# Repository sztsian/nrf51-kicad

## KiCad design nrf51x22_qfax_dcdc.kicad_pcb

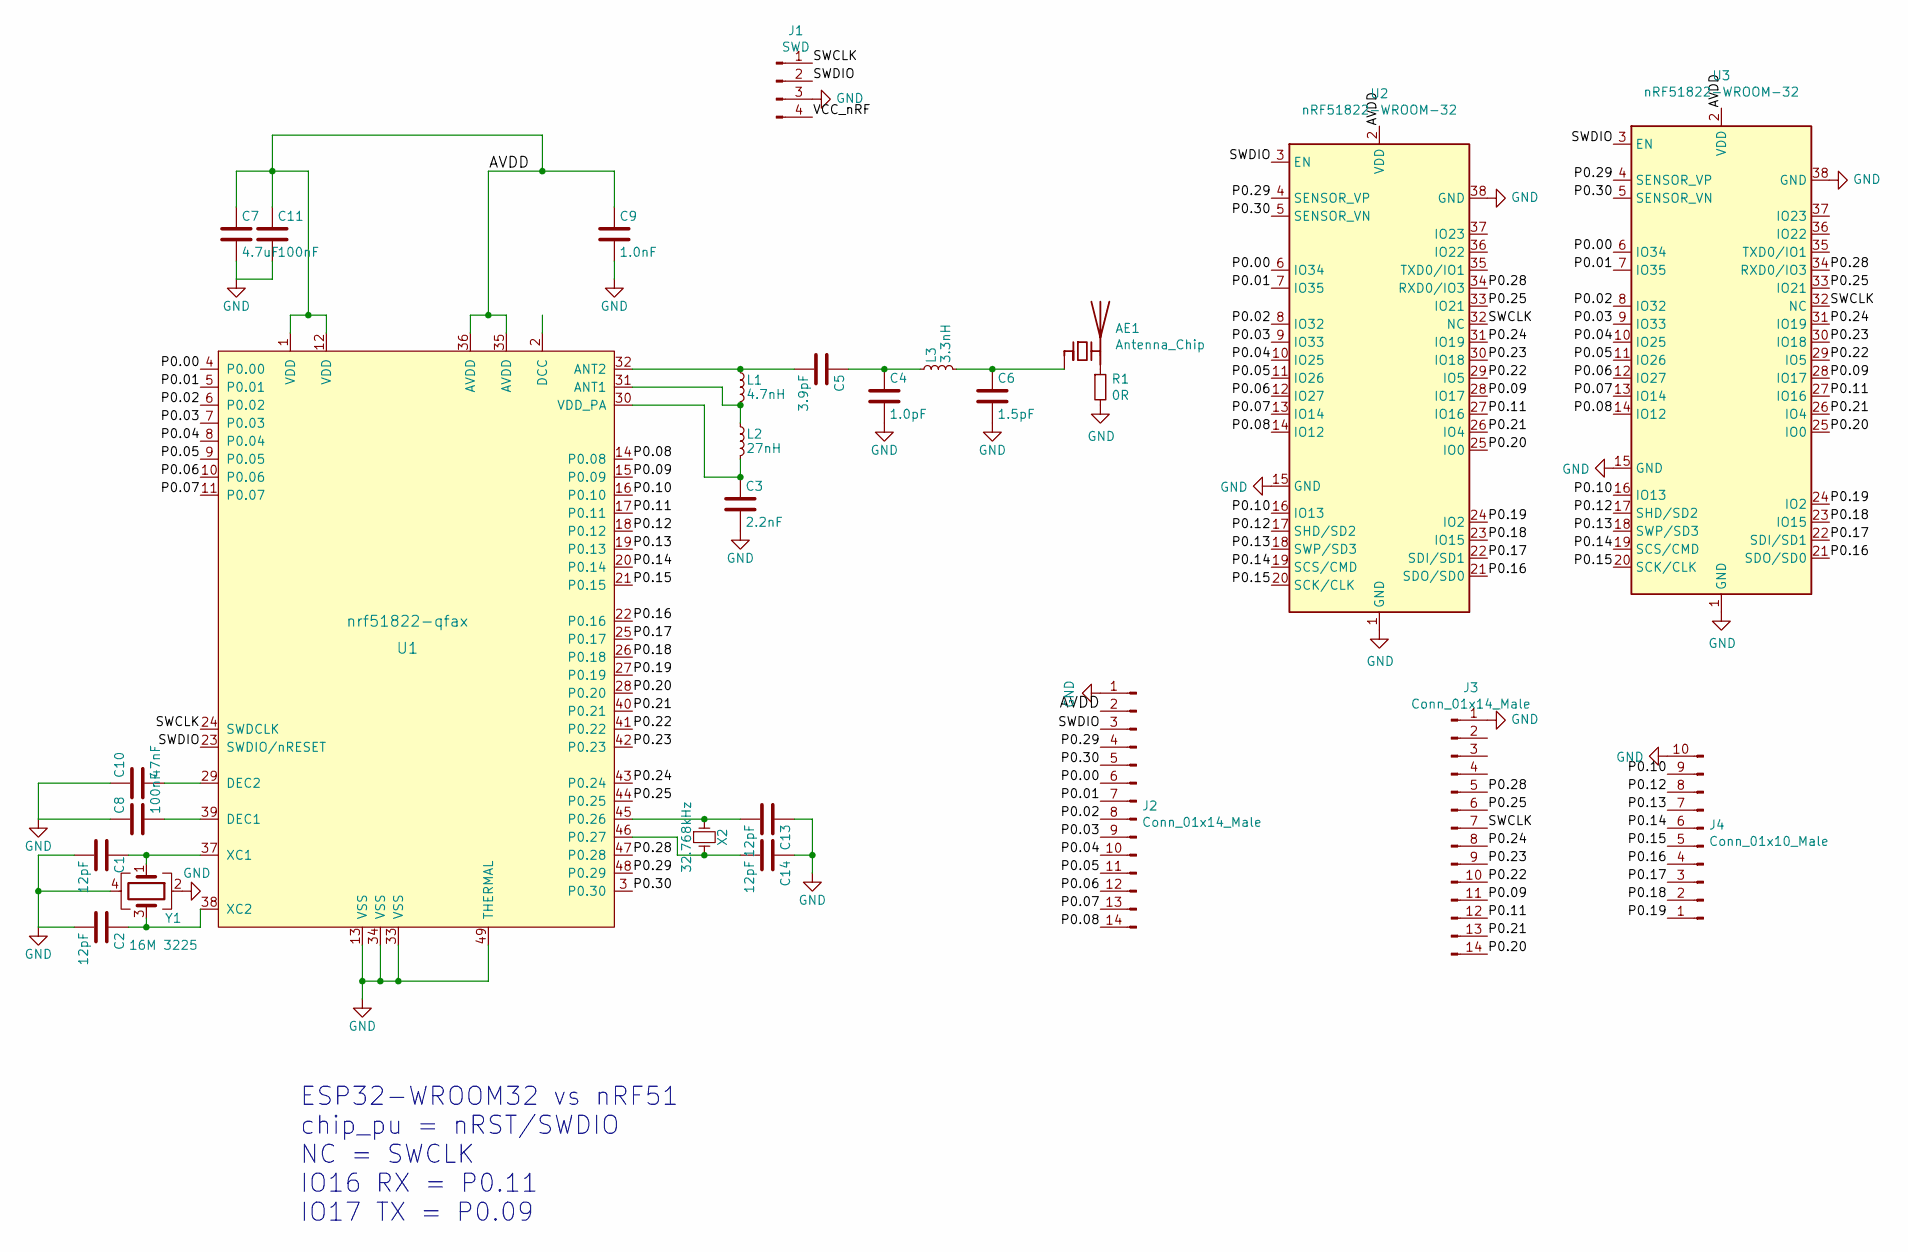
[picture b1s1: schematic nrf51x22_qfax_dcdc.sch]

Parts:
AE1: Antenna_Chip; Texas_SWRA117D_2.4GHz_Left
C1, C2, C13, C14: 12pF; C_0402_1005Metric; Manufacturer Part GRM1555C1H120GA01D
C3: 2.2nF; C_0402_1005Metric; Manufacturer Part CC0402KRX7R9BB222
C4: 1.0pF; C_0402_1005Metric
C5: 3.9pF; C_0402_1005Metric
C6: 1.5pF; C_0402_1005Metric
C7: 4.7uF; C_0402_1005Metric; Manufacturer Part GRM188R61C475KE11D
C8, C11: 100nF; C_0402_1005Metric; Manufacturer Part CC0402KRX7R6BB104
C9: 1.0nF; C_0402_1005Metric; Manufacturer Part CC0402KRX7R9BB102
C10: 47nF; C_0402_1005Metric; Manufacturer Part CC0402KRX7R8BB473
J1: SWD; PinHeader_1x04_P2.54mm_Vertical
J2, J3: Conn_01x14_Male; PinHeader_1x14_P1.27mm_Vertical
J4: Conn_01x10_Male; PinHeader_1x10_P1.27mm_Vertical
L1: 4.7nH; L_0402_1005Metric
L2: 27nH; L_0402_1005Metric
L3: 3.3nH; L_0402_1005Metric
R1: 0R; R_0402_1005Metric
U1: nrf51822-qfax; nrf51-qfax-1ep-vias; Manufacturer Part NRF51822-QFAC-T
U2, U3: nRF51822-WROOM-32; nRF51822-WROOM-32D
X2: 32.768kHz; Crystal_SMD_3215-2Pin_3.2x1.5mm; Manufacturer Part ABS07-32.768KHZ-9-T
Y1: 16M 3225; Crystal_SMD_2520-4Pin_2.5x2.0mm

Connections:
/AVDD: C7.1, C9.1, C11.1, J2.2, U1.1 (VDD), U1.12 (VDD), U1.35 (AVDD), U1.36 (AVDD), U2.2 (VDD), U3.2 (VDD)
/P0.00: J2.6, U1.4 (P0.00), U2.6 (IO34), U3.6 (IO34)
/P0.01: J2.7, U1.5 (P0.01), U2.7 (IO35), U3.7 (IO35)
/P0.02: J2.8, U1.6 (P0.02), U2.8 (IO32), U3.8 (IO32)
/P0.03: J2.9, U1.7 (P0.03), U2.9 (IO33), U3.9 (IO33)
/P0.04: J2.10, U1.8 (P0.04), U2.10 (IO25), U3.10 (IO25)
/P0.05: J2.11, U1.9 (P0.05), U2.11 (IO26), U3.11 (IO26)
/P0.06: J2.12, U1.10 (P0.06), U2.12 (IO27), U3.12 (IO27)
/P0.07: J2.13, U1.11 (P0.07), U2.13 (IO14), U3.13 (IO14)
/P0.08: J2.14, U1.14 (P0.08), U2.14 (IO12), U3.14 (IO12)
/P0.09: J3.11, U1.15 (P0.09), U2.28 (IO17), U3.28 (IO17)
/P0.10: J4.9, U1.16 (P0.10), U2.16 (IO13), U3.16 (IO13)
/P0.11: J3.12, U1.17 (P0.11), U2.27 (IO16), U3.27 (IO16)
/P0.12: J4.8, U1.18 (P0.12), U2.17 (SHD/SD2), U3.17 (SHD/SD2)
/P0.13: J4.7, U1.19 (P0.13), U2.18 (SWP/SD3), U3.18 (SWP/SD3)
/P0.14: J4.6, U1.20 (P0.14), U2.19 (SCS/CMD), U3.19 (SCS/CMD)
/P0.15: J4.5, U1.21 (P0.15), U2.20 (SCK/CLK), U3.20 (SCK/CLK)
/P0.16: J4.4, U1.22 (P0.16), U2.21 (SDO/SD0), U3.21 (SDO/SD0)
/P0.17: J4.3, U1.25 (P0.17), U2.22 (SDI/SD1), U3.22 (SDI/SD1)
/P0.18: J4.2, U1.26 (P0.18), U2.23 (IO15), U3.23 (IO15)
/P0.19: J4.1, U1.27 (P0.19), U2.24 (IO2), U3.24 (IO2)
/P0.20: J3.14, U1.28 (P0.20), U2.25 (IO0), U3.25 (IO0)
/P0.21: J3.13, U1.40 (P0.21), U2.26 (IO4), U3.26 (IO4)
/P0.22: J3.10, U1.41 (P0.22), U2.29 (IO5), U3.29 (IO5)
/P0.23: J3.9, U1.42 (P0.23), U2.30 (IO18), U3.30 (IO18)
/P0.24: J3.8, U1.43 (P0.24), U2.31 (IO19), U3.31 (IO19)
/P0.25: J3.6, U1.44 (P0.25), U2.33 (IO21), U3.33 (IO21)
/P0.28: J3.5, U1.47 (P0.28), U2.34 (RXD0/IO3), U3.34 (RXD0/IO3)
/P0.29: J2.4, U1.48 (P0.29), U2.4 (SENSOR_VP), U3.4 (SENSOR_VP)
/P0.30: J2.5, U1.3 (P0.30), U2.5 (SENSOR_VN), U3.5 (SENSOR_VN)
/SWDIO: J1.2, J2.3, U1.23 (SWDIO/nRESET), U2.3 (EN), U3.3 (EN)
/VCC_nRF: J1.4
GND: C1.2, C2.2, C3.2, C4.2, C6.2, C7.2, C8.1, C9.2, C10.1, C11.2, C13.1, C14.1, J1.3, J2.1, J3.1, J4.10, R1.2, U1.13 (VSS), U1.33 (VSS), U1.34 (VSS), U1.49 (THERMAL), U2.1 (GND), U2.15 (GND), U2.38 (GND), U3.1 (GND), U3.15 (GND), U3.38 (GND), Y1.2, Y1.4
unnamed: AE1.1 (FEED), C6.1, L3.2
unnamed: AE1.2 (PCB_Trace), R1.1
unnamed: C1.1, U1.37 (XC1), Y1.1
unnamed: C2.1, U1.38 (XC2), Y1.3
unnamed: C3.1, L2.2, U1.30 (VDD_PA)
unnamed: C4.1, C5.1, L3.1
unnamed: C5.2, L1.1, U1.32 (ANT2)
unnamed: C8.2, U1.39 (DEC1)
unnamed: C10.2, U1.29 (DEC2)
unnamed: C13.2, U1.45 (P0.26), X2.1
unnamed: C14.2, U1.46 (P0.27), X2.2
unnamed: L1.2, L2.1, U1.31 (ANT1)

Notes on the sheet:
ESP32-WROOM32 vs nRF51 chip_pu = nRST/SWDIO NC = SWCLK IO16 RX = P0.11 IO17 TX = P0.09

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
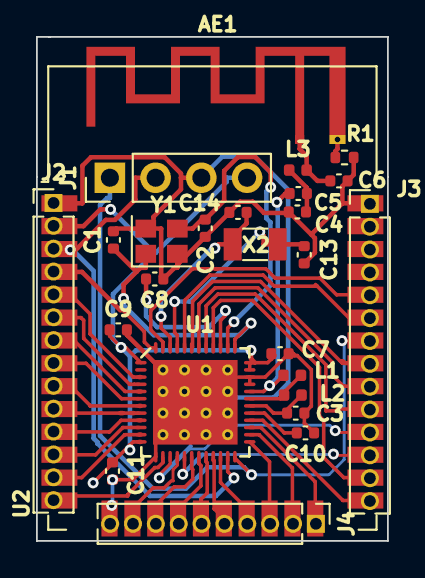
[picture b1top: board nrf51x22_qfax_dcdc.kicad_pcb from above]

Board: 2 copper layers, 19.5 x 28.0 mm, 27 parts (1 on the bottom side), 45 nets.

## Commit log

2020-12-30 WIP: Adding finished sch
2020-12-30 WIP: finish basic pcb. There are errors in gerber
